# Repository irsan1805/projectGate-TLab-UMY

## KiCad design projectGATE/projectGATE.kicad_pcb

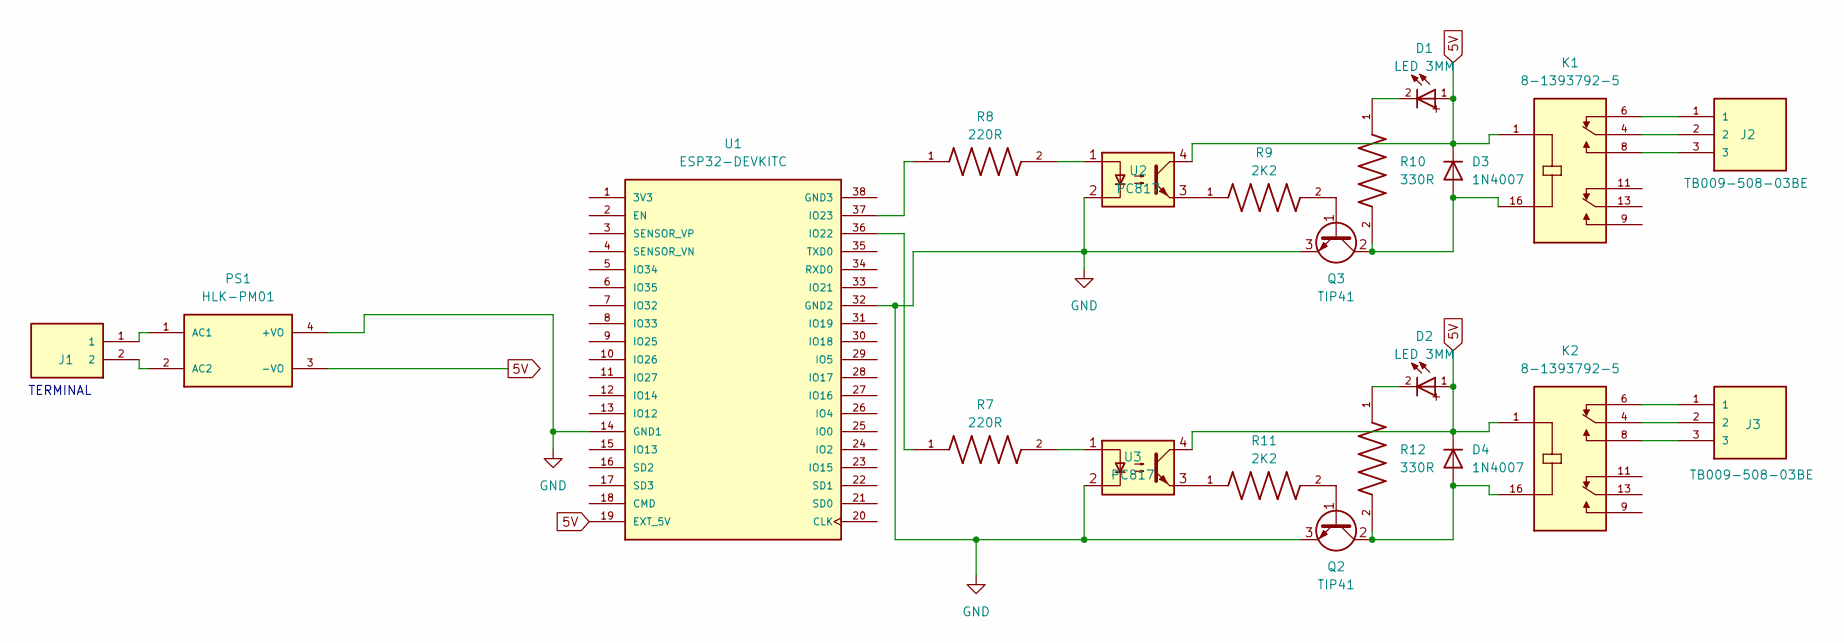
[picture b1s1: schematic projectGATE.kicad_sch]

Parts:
D1, D2: LED 3MM; WL-TMRC_3MM
D3, D4: 1N4007; D_DO-41_SOD81_P10.16mm_Horizontal
J1: TB009-508-02BE; CUI_TB009-508-02BE
J2, J3: TB009-508-03BE; CUI_TB009-508-03BE
K1, K2: 8-1393792-5; RELAY_8-1393792-5; PARTREV 1017
PS1: HLK-PM01; CONV_HLK-PM01
Q2, Q3: TIP41; TO-220-3_Vertical
R7, R8: 220R; RESAD1100W55L680D260; PARTREV 201304
R9, R11: 2K2; RESAD1100W55L680D260; PARTREV 201304
R10, R12: 330R; RESAD1100W55L680D260; PARTREV 201304
U1: ESP32-DEVKITC; MODULE_ESP32-DEVKITC; PARTREV N/A
U2, U3: PC817; DIP-4_W7.62mm

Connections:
5V: D1.1, D2.1, D3.1 (K), D4.1 (K), K1.1, K2.1, PS1.3 (-VO), U1.19 (EXT_5V), U2.4, U3.4
GND: PS1.4 (+VO), Q2.3 (E), Q3.3 (E), U1.14 (GND1), U1.32 (GND2), U2.2, U3.2
unnamed: D1.2, R10.1
unnamed: D2.2, R12.1
unnamed: D3.2 (A), K1.16, Q3.2 (C), R10.2
unnamed: D4.2 (A), K2.16, Q2.2 (C), R12.2
unnamed: J2.1, K1.6
unnamed: J2.2, K1.4
unnamed: J2.3, K1.8
unnamed: J3.1, K2.6
unnamed: J3.2, K2.4
unnamed: J3.3, K2.8
unnamed: J1.1, PS1.1 (AC1)
unnamed: J1.2, PS1.2 (AC2)
unnamed: Q2.1 (B), R11.2
unnamed: Q3.1 (B), R9.2
unnamed: R7.2, U3.1
unnamed: R8.2, U2.1
unnamed: R9.1, U2.3
unnamed: R11.1, U3.3
unnamed: R7.1, U1.36 (IO22)
unnamed: R8.1, U1.37 (IO23)

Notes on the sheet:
TERMINAL

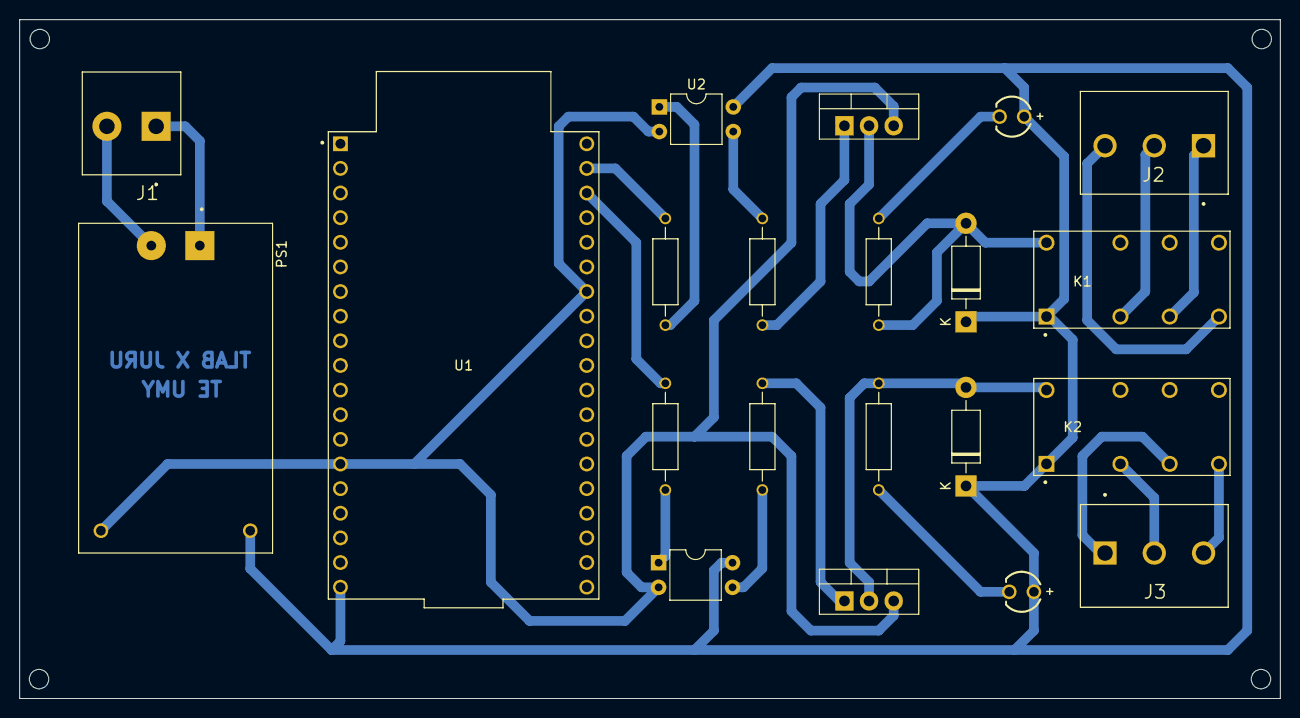
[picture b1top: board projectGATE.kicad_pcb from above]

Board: 2 copper layers, 130.0 x 70.0 mm, 21 parts (0 on the bottom side), 22 nets.

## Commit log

2024-10-28 Menambahkan Schematic dan desain PCB
2024-10-28 for you guys
2024-11-04 fixx
2024-11-14 menambahkan code untuk ESP32
